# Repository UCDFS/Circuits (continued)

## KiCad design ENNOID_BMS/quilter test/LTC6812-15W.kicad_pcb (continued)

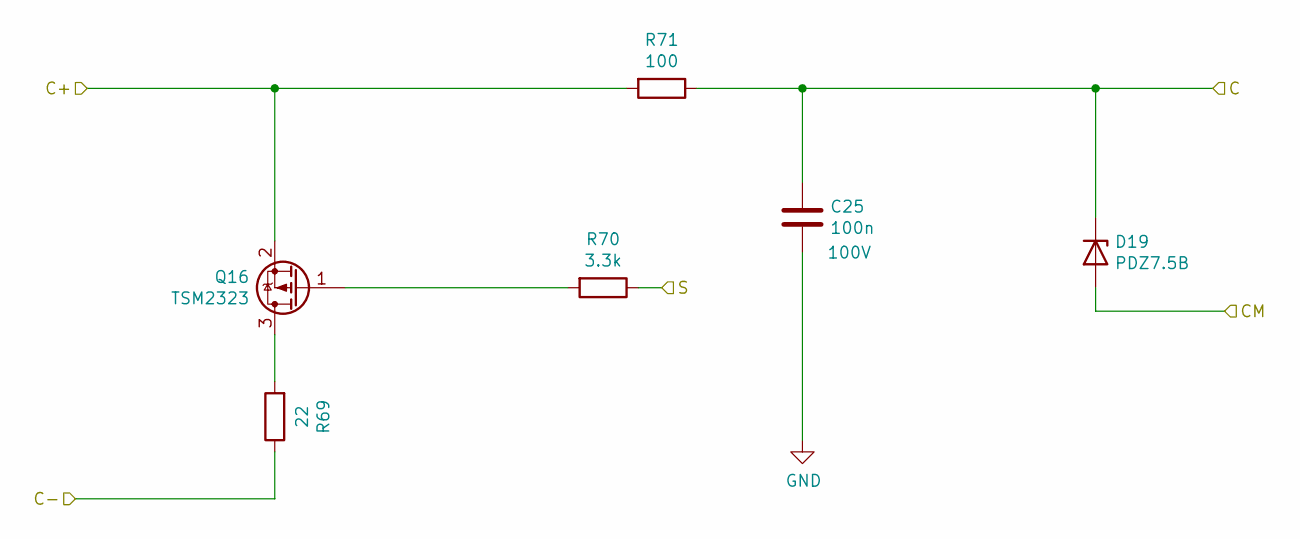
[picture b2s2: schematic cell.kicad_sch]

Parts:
C25: 100n; C_0603_1608Metric; Voltage 100V; Part Number GRM188R72A104KA35D
D19: PDZ7.5B; D_SOD-323; Part Number PDZ7.5B
Q16: TSM2323; SOT-23; Part Number TSM2323
R69: 22; R_2512_6332Metric; Part Number AC2512JK-7W22RL
R70: 3.3k; R_0603_1608Metric; Part Number CRCW06033K30FKEA
R71: 100; R_0603_1608Metric; Part Number CRCW0603100RFKEA

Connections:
/cell14/C: D19.2 (A); also elsewhere on the board
/cell15/C: C25.2, D19.1 (K), R71.1; also elsewhere on the board
/cell15/S: R70.1; also elsewhere on the board
Cell_1-: C25.1; also elsewhere on the board
Cell_14+: R69.1; also elsewhere on the board
Cell_15+: Q16.2 (S), R71.2; also elsewhere on the board
unnamed: Q16.3 (D), R69.2
unnamed: Q16.1 (G), R70.2

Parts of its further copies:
C11, C12, C13, C14, C15, C16, C17, C18, C19, C20, C21, C22, C23, C24: 100n; C_0603_1608Metric; Voltage 100V; Part Number GRM188R72A104KA35D
D5, D6, D7, D8, D9, D10, D11, D12, D13, D14, D15, D16, D17, D18: PDZ7.5B; D_SOD-323; Part Number PDZ7.5B
Q2, Q3, Q4, Q5, Q6, Q7, Q8, Q9, Q10, Q11, Q12, Q13, Q14, Q15: TSM2323; SOT-23; Part Number TSM2323
R13, R17, R21, R25, R29, R33, R37, R41, R45, R49, R53, R57, R61, R65: 22; R_2512_6332Metric; Part Number AC2512JK-7W22RL
R14, R18, R22, R26, R30, R34, R38, R42, R46, R50, R54, R58, R62, R66: 3.3k; R_0603_1608Metric; Part Number CRCW06033K30FKEA
R15, R19, R23, R27, R31, R35, R39, R43, R47, R51, R55, R59, R63, R67: 100; R_0603_1608Metric; Part Number CRCW0603100RFKEA

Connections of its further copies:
/cell1/C: C11.2, D5.1 (K), D6.2 (A), R15.1; also elsewhere on the board
/cell1/S: R14.1; also elsewhere on the board
/cell2/C: C12.2, D6.1 (K), D7.2 (A), R19.1; also elsewhere on the board
/cell2/S: R18.1; also elsewhere on the board
/cell3/C: C13.2, D7.1 (K), D8.2 (A), R23.1; also elsewhere on the board
/cell3/S: R22.1; also elsewhere on the board
/cell4/C: C14.2, D8.1 (K), D9.2 (A), R27.1; also elsewhere on the board
/cell4/S: R26.1; also elsewhere on the board
/cell5/C: C15.2, D9.1 (K), D10.2 (A), R31.1; also elsewhere on the board
/cell5/S: R30.1; also elsewhere on the board
/cell6/C: C16.2, D10.1 (K), D11.2 (A), R35.1; also elsewhere on the board
/cell6/S: R34.1; also elsewhere on the board
/cell7/C: C17.2, D11.1 (K), D12.2 (A), R39.1; also elsewhere on the board
/cell7/S: R38.1; also elsewhere on the board
/cell8/C: C18.2, D12.1 (K), D13.2 (A), R43.1; also elsewhere on the board
/cell8/S: R42.1; also elsewhere on the board
/cell9/S: R46.1; also elsewhere on the board
/cell10/C: C20.2, D14.1 (K), D15.2 (A), R51.1; also elsewhere on the board
/cell10/CM: C19.2, D13.1 (K), D14.2 (A), R47.1; also elsewhere on the board
/cell10/S: R50.1; also elsewhere on the board
/cell11/C: C21.2, D15.1 (K), D16.2 (A), R55.1; also elsewhere on the board
/cell11/S: R54.1; also elsewhere on the board
/cell12/C: C22.2, D16.1 (K), D17.2 (A), R59.1; also elsewhere on the board
/cell12/S: R58.1; also elsewhere on the board
/cell13/C: C23.2, D17.1 (K), D18.2 (A), R63.1; also elsewhere on the board
/cell13/S: R62.1; also elsewhere on the board
/cell14/C: C24.2, D18.1 (K), R67.1; also elsewhere on the board
/cell14/S: R66.1; also elsewhere on the board
Cell_1+: Q2.2 (S), R15.2, R17.1; also elsewhere on the board
Cell_1-: C11.1, C12.1, C13.1, C14.1, C15.1, C16.1, C17.1, C18.1, C19.1, C20.1, C21.1, C22.1, C23.1, C24.1, D5.2 (A), R13.1; also elsewhere on the board
Cell_2+: Q3.2 (S), R19.2, R21.1; also elsewhere on the board
Cell_3+: Q4.2 (S), R23.2, R25.1; also elsewhere on the board
Cell_4+: Q5.2 (S), R27.2, R29.1; also elsewhere on the board
Cell_5+: Q6.2 (S), R31.2, R33.1; also elsewhere on the board
Cell_6+: Q7.2 (S), R35.2, R37.1; also elsewhere on the board
Cell_7+: Q8.2 (S), R39.2, R41.1; also elsewhere on the board
Cell_8+: Q9.2 (S), R43.2, R45.1; also elsewhere on the board
Cell_9+: Q10.2 (S), R47.2, R49.1; also elsewhere on the board
Cell_10+: Q11.2 (S), R51.2, R53.1; also elsewhere on the board
Cell_11+: Q12.2 (S), R55.2, R57.1; also elsewhere on the board
Cell_12+: Q13.2 (S), R59.2, R61.1; also elsewhere on the board
Cell_13+: Q14.2 (S), R63.2, R65.1; also elsewhere on the board
Cell_14+: Q15.2 (S), R67.2; also elsewhere on the board
unnamed: Q2.3 (D), R13.2
unnamed: Q2.1 (G), R14.2
unnamed: Q3.3 (D), R17.2
unnamed: Q3.1 (G), R18.2
unnamed: Q4.3 (D), R21.2
unnamed: Q4.1 (G), R22.2
unnamed: Q5.3 (D), R25.2
unnamed: Q5.1 (G), R26.2
unnamed: Q6.3 (D), R29.2
unnamed: Q6.1 (G), R30.2
unnamed: Q7.3 (D), R33.2
unnamed: Q7.1 (G), R34.2
unnamed: Q8.3 (D), R37.2
unnamed: Q8.1 (G), R38.2
unnamed: Q9.3 (D), R41.2
unnamed: Q9.1 (G), R42.2
unnamed: Q10.3 (D), R45.2
unnamed: Q10.1 (G), R46.2
unnamed: Q11.3 (D), R49.2
unnamed: Q11.1 (G), R50.2
unnamed: Q12.3 (D), R53.2
unnamed: Q12.1 (G), R54.2
unnamed: Q13.3 (D), R57.2
unnamed: Q13.1 (G), R58.2
unnamed: Q14.3 (D), R61.2
unnamed: Q14.1 (G), R62.2
unnamed: Q15.3 (D), R65.2
unnamed: Q15.1 (G), R66.2

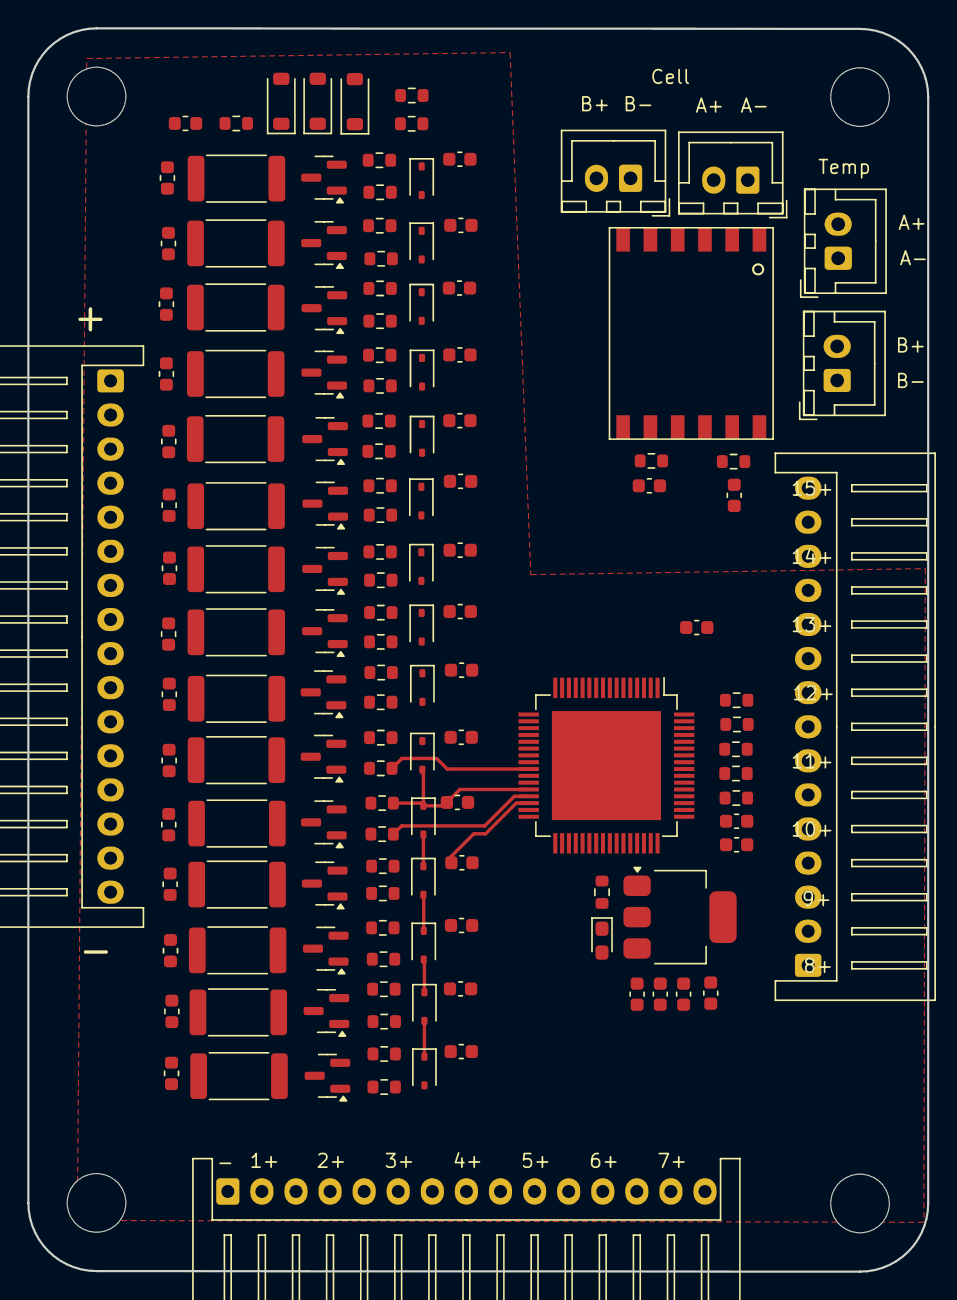
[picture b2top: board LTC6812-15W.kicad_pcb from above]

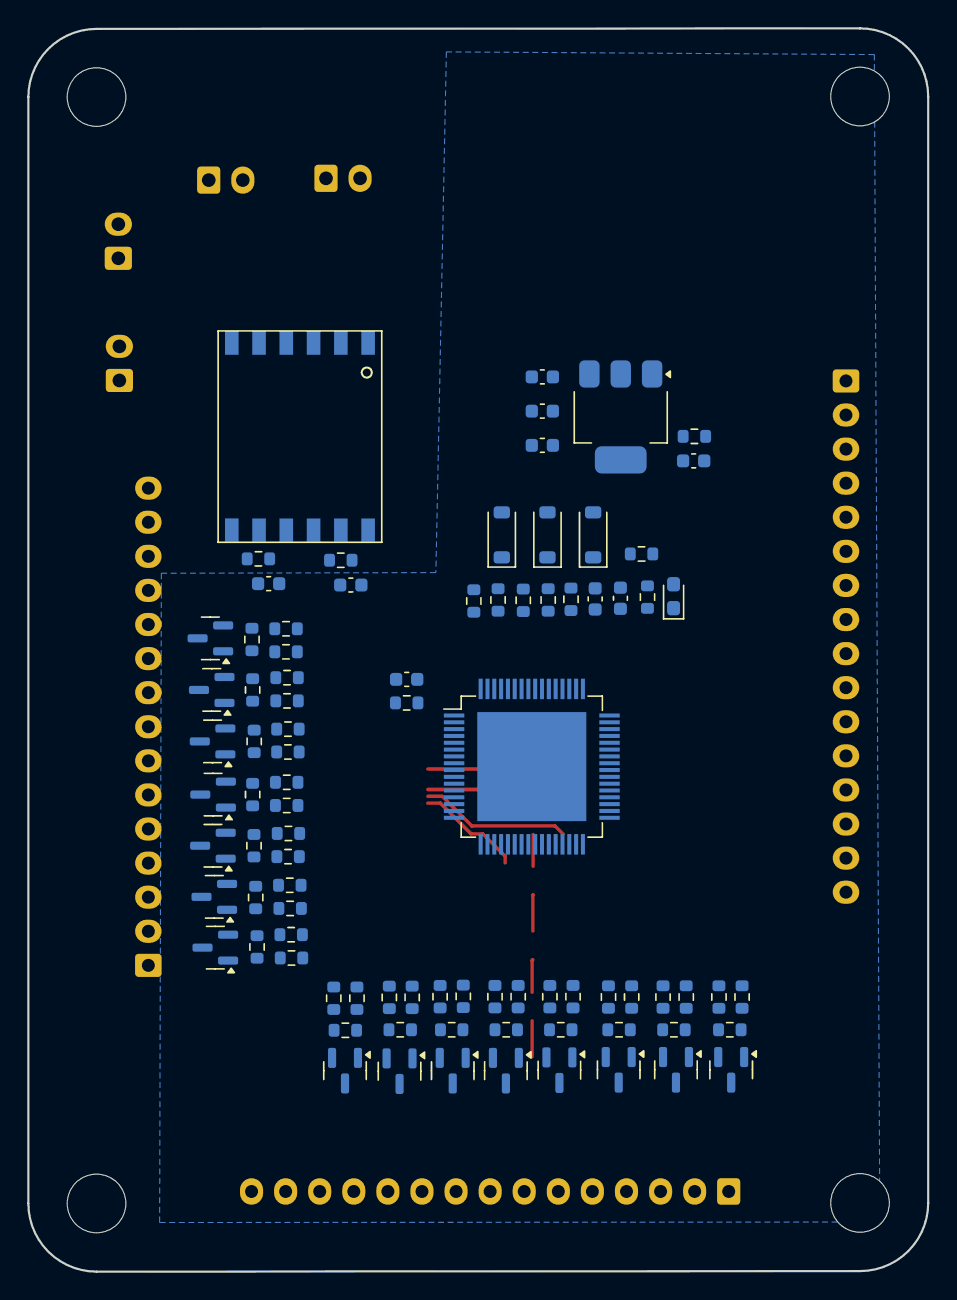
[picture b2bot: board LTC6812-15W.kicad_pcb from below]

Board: 2 copper layers, 66.0 x 91.2 mm, 227 parts (87 on the bottom side), 213 nets.

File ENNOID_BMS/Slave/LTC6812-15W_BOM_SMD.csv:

Reference,Qty,Value,DNP,Exclude from Board,Footprint,Datasheet,Part Number
"C1,C4,C10,C11,C12,C13,C14,C15,C16,C17,C18,C19,C20,C21,C22,C23,C24,C25,C28",19,100n,,,Capacitor_SMD:C_0603_1608Metric,https://pim.murata.com/asset/pim4/ceramicCapacitorSMD/GRM188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,GRM188R72A104KA35D
"C2,C3,C5,C6,C7,C26,C27,C29,C30,C31",10,1uF,,,Capacitor_SMD:C_0603_1608Metric,https://mm.digikey.com/Volume0/opasdata/d220001/medias/docus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,CL10B105KP8NNNC
"C8,C9,C32,C33",4,100p,,,Capacitor_SMD:C_0603_1608Metric,https://pim.murata.com/asset/pim4/ceramicCapacitorSMD/GRM188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,GRM1885C1H101JA01D
"D1,D2,D20,D21",4,1N4148W,,,Diode_SMD:D_SOD-123,https://www.mouser.ie/datasheet/3/175/1/BAV16W_1N4148W.pdf,1N4148W-7-F
"D3,D22",2,MMSZ5268BT1G,,,Diode_SMD:D_SOD-123,https://www.onsemi.com/pub/Collateral/MMSZ5221BT1-D.PDF,MMSZ5268BT1G
"D4,D23",2,LED,,,LED_SMD:LED_0603_1608Metric_Pad1.05x0.95mm_HandSolder,https://www.vishay.com/doc?84393,VLMTG1400-GS08
"D5,D6,D7,D8,D9,D10,D11,D12,D13,D14,D15,D16,D17,D18,D19",15,PDZ7.5B,,,Diode_SMD:D_SOD-323,https://assets.nexperia.com/documents/data-sheet/PDZ-B_SER.pdf,PDZ7.5B
"F4,F5,F6,F7,F8,F9,F10,F11,F12,F13,F14,F15,F16,F17,F18,F19",16,0.25A,,,Fuse:Fuse_0603_1608Metric,https://www.littelfuse.com/assetdocs/littelfuse_fuse_438_dat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,0438.250WR
"FB1,FB2",2,33,,,Resistor_SMD:R_0603_1608Metric,https://www.mouser.ie/datasheet/3/76/1/ENFA0003.pdf,BLM18PG330SN1D
"Q1,Q17",2,DZTT5551,,,Package_TO_SOT_SMD:SOT-223,https://www.mouser.ie/datasheet/3/175/1/ds31219.pdf,DZT5551-13
"Q2,Q3,Q4,Q5,Q6,Q7,Q8,Q9,Q10,Q11,Q12,Q13,Q14,Q15,Q16",15,TSM2323,,,Package_TO_SOT_SMD:SOT-23,https://www.taiwansemi.com/assets/datasheet/pdf.php?pn=TSM2323CX,TSM2323
"R1,R3,R8,R9,R15,R19,R23,R27,R31,R35,R39,R43,R47,R51,R55,R59,R63,R67,R71,R74,R76,R81,R82,R84,R85,R86,R87,R88,R89,R90,R91,R92,R93,R94,R95,R96,R98,R99",38,100,,,Resistor_SMD:R_0603_1608Metric,https://www.vishay.com/docs/20035/dcrcwe3.pdf,CRCW0603100RFKEA
"R2,R75",2,806,,,Resistor_SMD:R_0603_1608Metric,https://www.vishay.com/docs/20035/dcrcwe3.pdf,CRCW0603806RFKEA
"R4,R77",2,1M,,,Resistor_SMD:R_0603_1608Metric,https://www.vishay.com/docs/20035/dcrcwe3.pdf,CRCW06031M00FKEA
"R5,R10,R78,R83",4,1.2k,,,Resistor_SMD:R_0603_1608Metric,https://www.vishay.com/docs/20035/dcrcwe3.pdf,CRCW06031K20FKEA
"R6,R7,R79,R80",4,0,,,Resistor_SMD:R_0603_1608Metric,https://www.vishay.com/docs/20035/dcrcwe3.pdf,CRCW06030000Z0EA
"R11,R12,R16,R20,R24,R28,R32,R36,R40,R44,R48,R52,R56,R60,R64",15,680,,,Resistor_SMD:R_0603_1608Metric,https://www.vishay.com/docs/20035/dcrcwe3.pdf,CRCW0603680RFKEA
"R13,R17,R21,R25,R29,R33,R37,R41,R45,R49,R53,R57,R61,R65,R69",15,22,,,Resistor_SMD:R_2512_6332Metric,https://www.mouser.ie/datasheet/3/508/1/PYu-AC_51_RoHS_L_11.pdf,AC2512JK-7W22RL
"R14,R18,R22,R26,R30,R34,R38,R42,R46,R50,R54,R58,R62,R66,R70",15,3.3k,,,Resistor_SMD:R_0603_1608Metric,https://www.vishay.com/docs/20035/dcrcwe3.pdf,CRCW06033K30FKEA
"TR1,TR2",2,HM2102NL,,,ENNOID:HM2102NL,https://www.mouser.ie/datasheet/3/508/1/HM2102NL.pdf,HM2102NL
"U1,U2",2,LTC6812-1,,,ENNOID:TQFP-64-1EP_10x10mm_P0.5mm_EP8x8mm,https://www.analog.com/media/en/technical-documentation/data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,LTC6812-1

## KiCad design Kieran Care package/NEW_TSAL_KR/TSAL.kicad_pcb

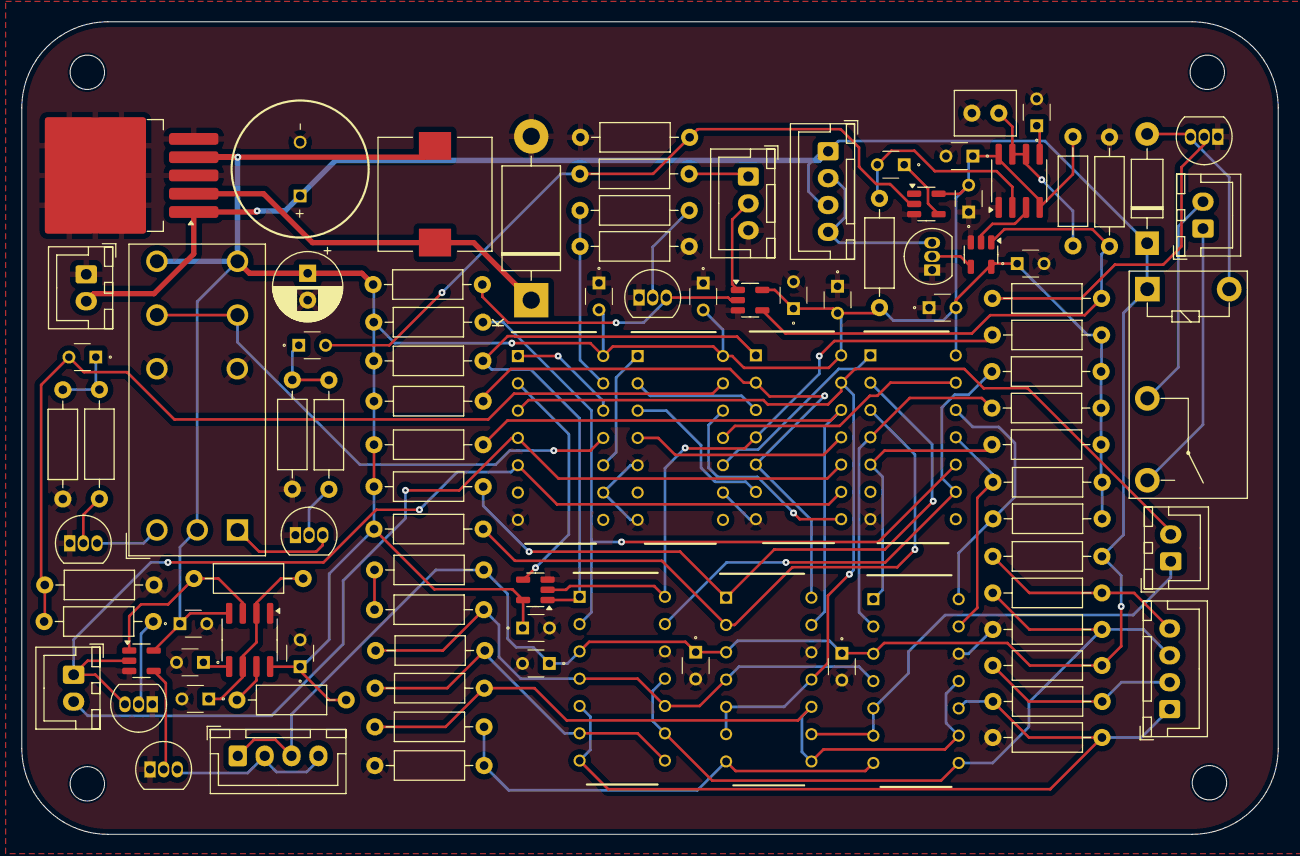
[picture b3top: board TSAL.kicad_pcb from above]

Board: 2 copper layers, 116.9 x 75.6 mm, 99 parts (0 on the bottom side), 71 nets.

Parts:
C1, C11, C28: 1uF; FA18X7R1H104KNU00
C2, C3, C4, C5, C6, C7, C8, C12, C13, C14, C16, C17, C22, C25, C26: 0.1uF; FA18X7R1H104KNU00
C9, C24: 10nF; FA18X7R1H104KNU00
C15: 220uF; CP_Radial_D6.3mm_P2.50mm
C18: 680uF; CAPPRD500W60D1275H2700
C23: 22uF; C_Disc_D5.5mm_W4mm_P2.50mm_1
D1: 1N4001; D_DO-41_SOD81_P10.16mm_Horizontal
D3: 1N5821; D_DO-201AD_P15.24mm_Horizontal
IC1, IC4, IC5: CD4072BE; DIP794W53P254L1930H508Q14N
IC3: SN74HC86N; DIP794W53P254L1930H508Q14N
J1, J4, J5: B4B-XH-A; JST_XH_B4B-XH-A_1x04_P2.50mm_Vertical
J2: B3B-XH-A; JST_XH_B3B-XH-A_1x03_P2.50mm_Vertical
J3, J6, J7, J8: B2B-XH-A; JST_XH_B2B-XH-A_1x02_P2.50mm_Vertical
K1: G5RL-K1-E-DC5; Relay-G5RL-K1-E
K2: G5Q1A4DC12; Relay_SPST_Omron-G5Q-1A
L1: 33uH; L_10.4x10.4_H4.8
Q1, Q2, Q3, Q4, Q5, Q6, Q7: 2N7000; TO-92_Inline
R1: 47k; R_Axial_DIN0207_L6.3mm_D2.5mm_P10.16mm_Horizontal
R2, R10, R11, R13, R14: 27k; R_Axial_DIN0207_L6.3mm_D2.5mm_P10.16mm_Horizontal
R3: 15k; R_Axial_DIN0207_L6.3mm_D2.5mm_P10.16mm_Horizontal
R4, R6, R51: 4.7k; R_Axial_DIN0207_L6.3mm_D2.5mm_P10.16mm_Horizontal
R5: 20k; R_Axial_DIN0207_L6.3mm_D2.5mm_P10.16mm_Horizontal
R7, R25, R36, R43, R44: 100; R_Axial_DIN0207_L6.3mm_D2.5mm_P10.16mm_Horizontal
R8, R23, R26, R39, R46: 10k; R_Axial_DIN0207_L6.3mm_D2.5mm_P10.16mm_Horizontal
R9, R12, R41, R42: 68k; R_Axial_DIN0207_L6.3mm_D2.5mm_P10.16mm_Horizontal
R15, R16, R17, R18, R19, R20, R21, R22, R29, R30, R31, R32: 5k6; R_Axial_DIN0207_L6.3mm_D2.5mm_P10.16mm_Horizontal
R24: 220k; R_Axial_DIN0207_L6.3mm_D2.5mm_P10.16mm_Horizontal
R27: 100k; R_Axial_DIN0207_L6.3mm_D2.5mm_P10.16mm_Horizontal
R40: 1k; R_Axial_DIN0207_L6.3mm_D2.5mm_P10.16mm_Horizontal
R50: 6k8; R_Axial_DIN0207_L6.3mm_D2.5mm_P10.16mm_Horizontal
U1, U7: SN74AHC1G32TDBVRQ1; SOT-23-5
U2, U6: LMC555CMX/NOPB; SOIC-8_3.9x4.9mm_P1.27mm
U3, U4, U5: LM339N/NOPB; DIP794W53P254L1930H508Q14N
U8, U14: SN74AHCT1G08DBVR; SOT-23-5
U9: SN74AHC1G04DBVRE4; SOT-23-5
U26: LM2596SX-5.0/NOPB; TO-263-5_TabPin3

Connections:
0V5th: R5.1, R6.2, U4.7 (+), U5.7 (+)
2V5th: R4.1, R5.2, U4.8 (-), U4.10 (-), U5.9 (+), U5.11 (+)
3Vth: R3.1, R4.2, U3.6 (-), U3.8 (-)
4V5th: R2.1, R3.2, U3.4 (-), U3.10 (-), U4.4 (-), U5.4 (-)
5V: C2.1, C4.2, C6.1, C7.1, C8.2, C13.1, C14.1, C15.1, C16.2, C17.2, C22.1, C26.2, IC1.14 (VDD), IC3.14 (VCC), IC4.14 (VDD), IC5.14 (VDD), K1.4, K1.5, K1.9, L1.2, R15.2, R16.2, R17.2, R18.2, R19.2, R20.2, R21.2, R22.2, R23.1, R27.1, R29.2, R30.2, R31.2, R32.2, R40.2, R46.1, U1.5 (VCC), U2.4 (R), U2.8 (VCC), U6.4 (R), U6.8 (VCC), U7.5 (VCC), U8.5 (VCC), U9.5 (VCC), U14.5 (VCC), U26.4 (FB)
7Vth: R1.1, R2.2
12V: C3.1, C5.1, C12.1, C18.1 (+), D1.1 (K), J4.1, J4.3, J5.1, J5.3, J6.2, K2.1, R1.2, R9.2, R12.2, U3.3 (V+), U4.3 (V+), U5.3 (V+), U26.1 (VIN)
A1: J1.1, R10.1, R11.2, U3.5 (+), U3.7 (+), U5.10 (-)
A2: J1.3, R13.1, R14.2, U3.9 (+), U3.11 (+), U5.8 (-)
AIR1_aux+: J1.2, R9.1, R10.2
AIR2_aux+: J1.4, R12.1, R13.2
AIR_CON_FAULT: IC4.10 (F), IC5.1 (J=A+B+C+D)
BATT_FAULT: IC3.8 (3Y), IC4.12 (H)
CON_buf: IC3.12 (4A), R21.1, U4.13
CON_imp: IC3.11 (4Y), IC4.4 (C)
GLVS 5V+: C28.2, R50.2, R51.1, U9.2
GLVS+: J2.1, R50.1
GLVS-: C2.2, C3.2, C4.1, C5.2, C6.2, C7.2, C8.1, C9.2, C11.2, C12.2, C13.2, C14.2, C15.2, C16.1, C17.1, C18.2 (-), C22.2, C23.1, C24.2, C26.1, D3.2 (A), IC1.7 (VSS), IC1.9 (E), IC3.7 (GND), IC4.5 (D), IC4.7 (VSS), IC4.9 (E), IC5.7 (VSS), J2.3, J6.1, K1.2, K1.7, Q1.1 (S), Q2.1 (S), Q3.1 (S), Q4.1 (S), Q5.1 (S), Q6.1 (S), Q7.1 (S), R6.1, R8.2, R11.1, R14.1, R26.1, R39.1, R41.1, R42.2, R51.2, U1.3 (GND), U2.1 (GND), U3.12 (V-), U4.12 (V-), U5.12 (V-), U6.1 (GND), U7.3 (GND), U8.3 (GND), U9.3 (GND), U14.3 (GND), U26.3 (GND), U26.5 (~ON/OFF)
IMP_FAULT: IC1.10 (F), IC4.1 (J=A+B+C+D)
unnamed: C1.1, R41.2, R43.2
unnamed: C25.1, U9.4
unnamed: C28.1, R42.1, R44.2
unnamed: D1.2 (A), K2.5, Q5.3 (D)
unnamed: D3.1 (K), L1.1, U26.2 (OUT)
unnamed: Q1.2 (G), R25.2
unnamed: Q2.2 (G), U8.4
unnamed: Q3.3 (D), R40.1, U14.2
unnamed: Q3.2 (G), R36.2
unnamed: Q4.2 (G), U7.4
unnamed: Q5.2 (G), R7.2
unnamed: K1.1, Q6.3 (D)
unnamed: Q6.2 (G), R44.1
unnamed: K1.8, Q7.3 (D)
unnamed: Q7.2 (G), R43.1
unnamed: C24.1, U2.5 (CV)
unnamed: C23.2, R27.2, U2.6 (THR), U2.7 (DIS)
unnamed: U2.3 (Q), U7.2
unnamed: C25.2, R46.2, U2.2 (TR)
unnamed: C9.1, U6.5 (CV)
unnamed: R23.2, U6.7 (DIS)
unnamed: R24.1, U6.3 (Q), U8.1
unnamed: C11.1, R24.2, U6.2 (TR), U6.6 (THR)
OPEN_CON: IC5.2 (A), R20.1, U4.1
OPEN_~AIR: IC5.5 (D), R30.1, U5.1
Precharge_ON: IC1.3 (B), IC3.13 (4B), J8.2, U4.5 (+), U4.6 (-), U4.11 (+)
Precharge_done/Close_AIR1: J8.1, U4.9 (+), U5.5 (+), U5.6 (-)
SCS_FAULT: C1.2, IC4.13 (K=E+F+G+H), R25.1, R26.2
SCS_LATCH: IC1.11 (G), K1.3, K1.6
SHORT_CON: IC5.3 (B), R19.1, U4.2
SHORT_~AIR: IC5.4 (C), R29.1, U5.2
TS<60V: J2.2, U14.1
TS>60V (1): IC1.4 (C), IC3.10 (3B), J3.2
TS>60V (2): IC1.5 (D), IC3.9 (3A), J3.1, Q1.3 (D), U8.2
TSAL_OK: R7.1, R8.1, U7.1, U14.4
TSAL_OK_Shutdown+: J7.1, K2.3
TSAL_OK_Shutdown-: J7.2, K2.2
TS_active: IC1.1 (J=A+B+C+D), IC1.12 (H)
air1_imp: IC3.3 (1Y), IC4.2 (A)
air2_imp: IC3.6 (2Y), IC4.3 (B)
closed_air: IC1.2 (A), U1.4
closed_air1: IC3.1 (1A), R16.1, U1.1, U3.1
closed_air2: IC3.4 (2A), R18.1, U1.2, U3.14
green-: J5.2, J5.4, Q4.3 (D)
not_green: IC1.13 (K=E+F+G+H), R36.1, R39.2
red-: J4.2, J4.4, Q2.3 (D)
short_air: IC4.11 (G), IC5.13 (K=E+F+G+H)
short_air1: IC5.10 (F), R15.1, U3.2
short_air2: IC5.9 (E), R17.1, U3.13
short_gnd_a1: IC5.11 (G), R31.1, U5.13
short_gnd_a2: IC5.12 (H), R32.1, U5.14
~AIR_buf: IC3.2 (1B), IC3.5 (2B), R22.1, U4.14

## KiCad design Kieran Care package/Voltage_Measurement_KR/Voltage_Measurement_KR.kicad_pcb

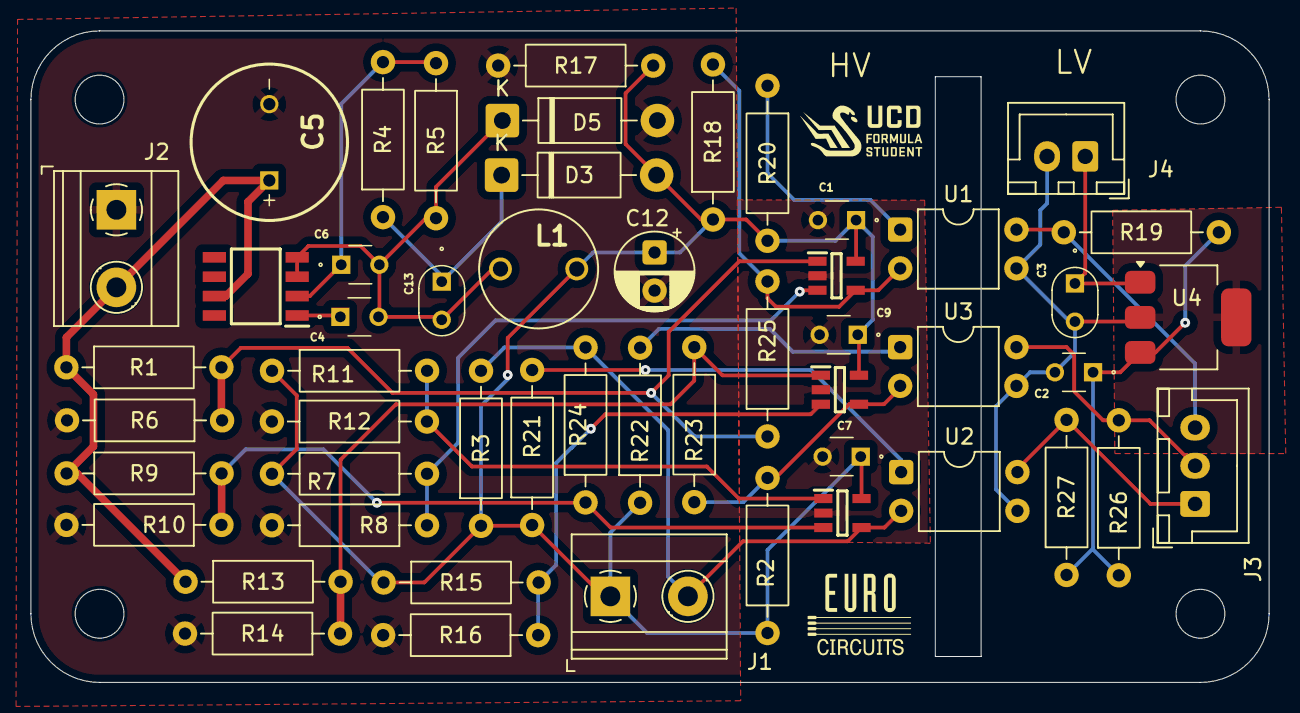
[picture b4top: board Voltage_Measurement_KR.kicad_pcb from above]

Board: 2 copper layers, 81.2 x 42.7 mm, 52 parts (0 on the bottom side), 25 nets.

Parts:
C1, C2, C7, C9: 0.1uF; FA18X7R1H104KNU00
C3, C13: 0.22uF; FA14X7R1H224KNU00
C4: 1uF; FA18X7R1H104KNU00
C5: 10uF 400VDC; CAPPRD500W60D1025H2200
C6: 470pF; FA18X7R1H104KNU00
C12: 10uF; CP_Radial_D5.0mm_P2.50mm
D3, D5: STTH1R06; D_DO-41_SOD81_P10.16mm_Horizontal
IC1: MP9488GS-P; SOIC127P600X175-8N
IC2, IC3, IC4: TLV1701AIDBVT; SOT95P280X145-5N
J1, J2: Conn_01x02_Phoenix; Phoenix_1x2_1729128
J3: Conn_01x03_Pin; JST_XH_B3B-XH-A_1x03_P2.50mm_Vertical
J4: Conn_01x02_Pin; JST_XH_B2B-XH-A_1x02_P2.50mm_Vertical
L1: 1.2mH; WE-TI_809589
R1, R9, R13: 560k; R_Axial_DIN0207_L6.3mm_D2.5mm_P10.16mm_Horizontal
R2, R3, R18: 100K; R_Axial_DIN0207_L6.3mm_D2.5mm_P10.16mm_Horizontal
R4, R6, R10, R14: 18k; R_Axial_DIN0207_L6.3mm_D2.5mm_P10.16mm_Horizontal
R5: 4.7k; R_Axial_DIN0207_L6.3mm_D2.5mm_P10.16mm_Horizontal
R7, R11, R15: 56k; R_Axial_DIN0207_L6.3mm_D2.5mm_P10.16mm_Horizontal
R8, R12, R16: 10k; R_Axial_DIN0207_L6.3mm_D2.5mm_P10.16mm_Horizontal
R17: 2.7k; R_Axial_DIN0207_L6.3mm_D2.5mm_P10.16mm_Horizontal
R19, R26, R27: 10K; R_Axial_DIN0207_L6.3mm_D2.5mm_P10.16mm_Horizontal
R20, R21, R22: 2.2K; R_Axial_DIN0207_L6.3mm_D2.5mm_P10.16mm_Horizontal
R23, R24, R25: 1.5M; R_Axial_DIN0207_L6.3mm_D2.5mm_P10.16mm_Horizontal
U1, U2, U3: HCPL-817-000E; DIP-4_W7.62mm
U4: LM7805_SOT223; SOT-223-3_TabPin2

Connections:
5V: C2.1, R19.1, R26.1, R27.1, U4.3 (VO)
12.3V: C1.1, C7.1, C9.1, C12.1, D3.2 (A), IC2.5 (V+), IC3.5 (V+), IC4.5 (V+), J1.1, L1.1, R2.1, R3.1, R7.1, R11.1, R15.1, R17.1, R18.1, R20.2, R21.1, R22.1
60V_REF_1: IC2.3 (IN-), R7.2, R8.1
60V_REF_2: IC3.1 (IN+), R11.2, R12.1
60V_REF_3: IC4.3 (IN-), R15.2, R16.1
300V_REF_1: IC2.1 (IN+), R1.2, R6.1, R25.1
300V_REF_2: IC3.3 (IN-), R9.2, R10.1, R24.1
300V_REF_3: IC4.1 (IN+), R13.2, R14.1, R23.1
GLV+: C3.1, J4.1, U4.1 (VI)
GLV-: C2.2, C3.2, J4.2, U1.3, U2.3, U3.3, U4.2 (GND)
LED-: IC3.4 (OUT), J1.2, R3.2, R24.2, U2.2
unnamed: C13.1, D3.1 (K), R4.1
unnamed: C4.2, C6.2, C13.2, D5.1 (K), IC1.3 (SW_1), IC1.4 (SW_2), L1.2, R5.2
unnamed: C6.1, IC1.2 (FB), R4.2, R5.1
unnamed: C4.1, IC1.1 (VCC)
unnamed: IC2.4 (OUT), R18.2, R25.2, U1.2
unnamed: IC4.4 (OUT), R2.2, R23.2, U3.2
unnamed: R20.1, U1.1
unnamed: R21.2, U2.1
unnamed: R22.2, U3.1
TS+: C5.1 (+), IC1.7 (VIN), J2.2, R1.1, R9.1, R13.1
TS-: C1.2, C5.2 (-), C7.2, C9.2, C12.2, D5.2 (A), IC2.2 (V-), IC3.2 (V-), IC4.2 (V-), J2.1, R6.2, R8.2, R10.2, R12.2, R14.2, R16.2, R17.2
TS<60V: J3.1, R27.2, U2.4
TS>60V (1): J3.3, R19.2, U1.4
TS>60V (2): J3.2, R26.2, U3.4

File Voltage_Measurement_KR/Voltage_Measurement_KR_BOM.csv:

"Reference","Value","Part number","Datasheet","Footprint","Qty","DNP","Part Number"
"C1,C2,C7,C9,C10,C11,C14","0.1uF","FA18X7R1H104KNU00","https://www.farnell.com/datasheets/2923220.pdf","FA14_Capacitor:FA18X7R1H104KNU00","7","",""
"C3,C13","0.22uF","FA14X7R1H224KNU00","https://www.farnell.com/datasheets/2923220.pdf","FA14_Capacitor:FA14X7R1H224KNU00","2","",""
"C4","1uF","FA18X7R1E105KRU00","https://www.farnell.com/datasheets/2923220.pdf","FA14_Capacitor:FA18X7R1H104KNU00","1","",""
"C5","10uF 400VDC","400BXC10MEFC10X20","http://www.farnell.com/datasheets/2321684.pdf","400BXC10MEFC10X20:CAPPRD500W60D1025H2200","1","",""
"C6","470pF","FA18C0G1H471JNU00","https://www.farnell.com/datasheets/2923220.pdf","FA14_Capacitor:FA18X7R1H104KNU00","1","",""
"C12","10uF","ECE-A1EKS100I","https://industrial.panasonic.com/cdbs/www-data/pdf/RDF0000/A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","Capacitor_THT:CP_Radial_D5.0mm_P2.50mm","1","",""
"D3,D5","STTH1R06","STTH1R06","https://www.mouser.ie/datasheet/2/389/stth1r06-1851882.pdf","Diode_THT:D_DO-41_SOD81_P10.16mm_Horizontal","2","",""
"IC1","MP9488GS-P","MP9488GS-P","https://www.monolithicpower.com/en/documentview/productdocum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","MP9488GS-Z:SOIC127P600X175-8N","1","",""
"IC2,IC3,IC4","TLV1701AIDBVT","TLV1701AIDBVT","http://www.ti.com/lit/gpn/tlv1701","TLV1701AIDBVT:SOT95P280X145-5N","3","",""
"J1,J2","Conn_01x02_Phoenix","1729128","https://www.phoenixcontact.com/en-us/products/printed-circui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","Phoenix 1x2 Connector:Phoenix_1x2_1729128","2","",""
"J3","Conn_01x03_Pin","B3B-XH-A","https://www.jst-mfg.com/product/pdf/eng/eXH.pdf","Connector_JST:JST_XH_B3B-XH-A_1x03_P2.50mm_Vertical","1","",""
"J4","Conn_01x02_Pin","B2B-XH-A","https://www.jst-mfg.com/product/pdf/eng/eXH.pdf","Connector_JST:JST_XH_B2B-XH-A_1x02_P2.50mm_Vertical","1","",""
"L1","1.2mH","7447720122","https://www.we-online.com/components/products/datasheet/7447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","Inductor_7447720122:WE-TI_809589","1","",""
"Q1,Q2","2N7000","2N7000","https://www.onsemi.com/download/data-sheet/pdf/nds7002a-d.pdf","Package_TO_SOT_THT:TO-92_Inline","2","",""
"R1,R9,R13","560k","MCF 0.25W 560K","https://www.farnell.com/datasheets/3436052.pdf?_gl=1*1pxxutc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","Resistor_THT:R_Axial_DIN0207_L6.3mm_D2.5mm_P10.16mm_Horizontal","3","",""
"R2,R3,R18,R19,R20,R26,R27","1K","MCF 0.25W 1K","https://www.farnell.com/datasheets/3436052.pdf?_gl=1*1pxxutc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","Resistor_THT:R_Axial_DIN0207_L6.3mm_D2.5mm_P10.16mm_Horizontal","7","",""
"R4,R6,R10,R14","18k","MCF 0.25W 18K","https://www.farnell.com/datasheets/3436052.pdf?_gl=1*1pxxutc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","Resistor_THT:R_Axial_DIN0207_L6.3mm_D2.5mm_P10.16mm_Horizontal","4","",""
"R5","4.7k","MCF 0.25W 4.7K","https://www.farnell.com/datasheets/3436052.pdf?_gl=1*1pxxutc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","Resistor_THT:R_Axial_DIN0207_L6.3mm_D2.5mm_P10.16mm_Horizontal","1","",""
"R7,R11,R15","56k","MCF 0.25W 56K","https://www.farnell.com/datasheets/3436052.pdf?_gl=1*1pxxutc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","Resistor_THT:R_Axial_DIN0207_L6.3mm_D2.5mm_P10.16mm_Horizontal","3","",""
"R8,R12,R16","10k","MCF 0.25W 10K","https://www.farnell.com/datasheets/3436052.pdf?_gl=1*1pxxutc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","Resistor_THT:R_Axial_DIN0207_L6.3mm_D2.5mm_P10.16mm_Horizontal","3","",""
"R17","2.7k","MCF 0.25W 2K7","https://www.farnell.com/datasheets/3436052.pdf?_gl=1*1pxxutc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","Resistor_THT:R_Axial_DIN0207_L6.3mm_D2.5mm_P10.16mm_Horizontal","1","",""
"U1,U2,U3","HCPL-817-000E","HCPL-817-000E","https://www.mouser.ie/datasheet/2/678/AV02_0265EN_2021_04_26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","Package_DIP:DIP-4_W7.62mm","3","",""
"U4","LM7805_SOT223","LM7805MPX/NOPB","https://www.ti.com/lit/gpn/lm7800","Package_TO_SOT_SMD:SOT-223-3_TabPin2","1","",""

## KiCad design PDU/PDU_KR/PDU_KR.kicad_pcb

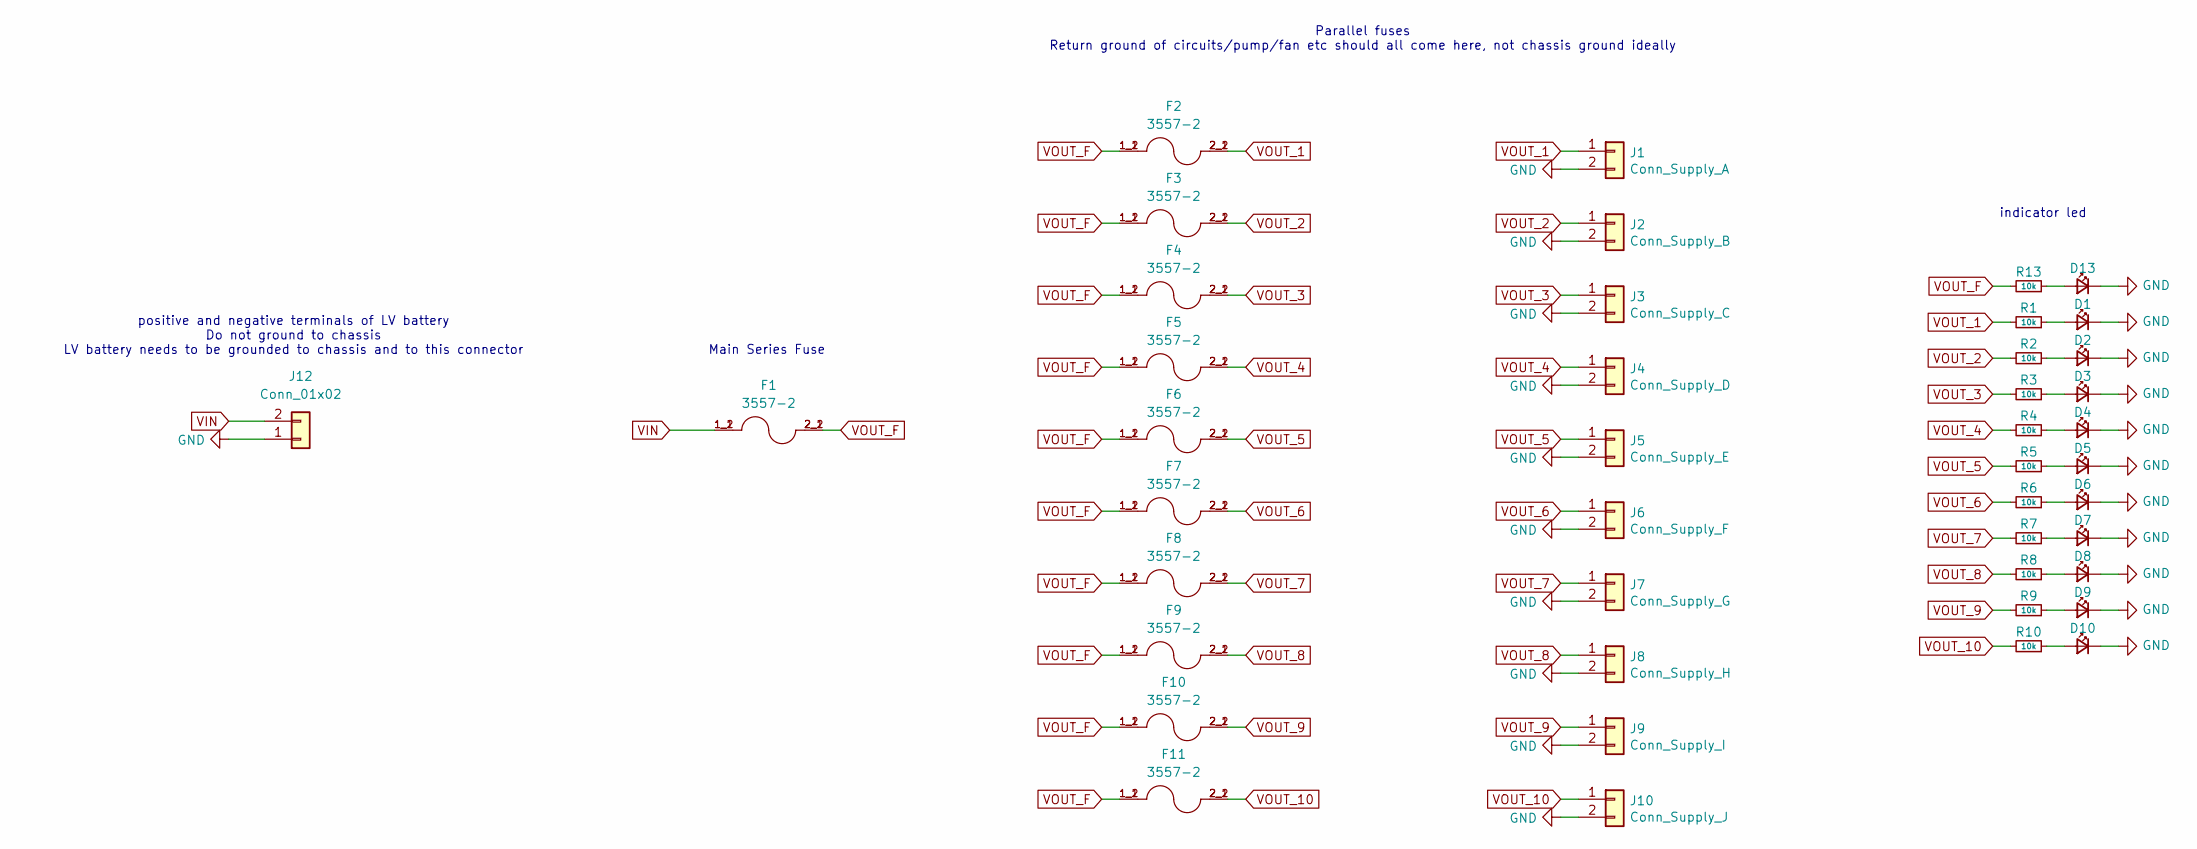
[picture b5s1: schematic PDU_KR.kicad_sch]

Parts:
D1, D2, D3, D4, D5, D6, D7, D8, D9, D10, D13: LED_Red; LED_0805_2012Metric; Manufacturer Part Number APT2012SECK/J3-PRV
F1, F2, F3, F4, F5, F6, F7, F8, F9, F10, F11: 3557-2; FUSE_3557-2; MPN 3557-2
J1: Conn_Supply_A; JST_XH_B2B-XH-A_1x02_P2.50mm_Vertical; Manufacturer Part Number B2B-XH-A
J2: Conn_Supply_B; JST_XH_B2B-XH-A_1x02_P2.50mm_Vertical; Manufacturer Part Number B2B-XH-A
J3: Conn_Supply_C; JST_XH_B2B-XH-A_1x02_P2.50mm_Vertical; Manufacturer Part Number B2B-XH-A
J4: Conn_Supply_D; JST_XH_B2B-XH-A_1x02_P2.50mm_Vertical; Manufacturer Part Number B2B-XH-A
J5: Conn_Supply_E; JST_XH_B2B-XH-A_1x02_P2.50mm_Vertical; Manufacturer Part Number B2B-XH-A
J6: Conn_Supply_F; JST_XH_B2B-XH-A_1x02_P2.50mm_Vertical; Manufacturer Part Number B2B-XH-A
J7: Conn_Supply_G; JST_XH_B2B-XH-A_1x02_P2.50mm_Vertical; Manufacturer Part Number B2B-XH-A
J8: Conn_Supply_H; JST_XH_B2B-XH-A_1x02_P2.50mm_Vertical; Manufacturer Part Number B2B-XH-A
J9: Conn_Supply_I; JST_XH_B2B-XH-A_1x02_P2.50mm_Vertical; Manufacturer Part Number B2B-XH-A
J10: Conn_Supply_J; JST_XH_B2B-XH-A_1x02_P2.50mm_Vertical; Manufacturer Part Number B2B-XH-A
J12: Conn_01x02; Phoenix_1x2_1729128; Manufacturer Part Number 1729128
R1, R2, R3, R4, R5, R6, R7, R8, R9, R10, R13: 10k; R_0805_2012Metric; Manufacturer Part Number RT0805FRE1010KL

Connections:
GND: D1.1 (K), D2.1 (K), D3.1 (K), D4.1 (K), D5.1 (K), D6.1 (K), D7.1 (K), D8.1 (K), D9.1 (K), D10.1 (K), D13.1 (K), J1.2, J2.2, J3.2, J4.2, J5.2, J6.2, J7.2, J8.2, J9.2, J10.2, J12.1
unnamed: D1.2 (A), R1.1
unnamed: D2.2 (A), R2.1
unnamed: D3.2 (A), R3.1
unnamed: D4.2 (A), R4.1
unnamed: D5.2 (A), R5.1
unnamed: D6.2 (A), R6.1
unnamed: D7.2 (A), R7.1
unnamed: D8.2 (A), R8.1
unnamed: D9.2 (A), R9.1
unnamed: D10.2 (A), R10.1
unnamed: D13.2 (A), R13.1
VIN: F1.1_1, F1.1_2, J12.2
VOUT_1: F2.2_1, F2.2_2, J1.1, R1.2
VOUT_2: F3.2_1, F3.2_2, J2.1, R2.2
VOUT_3: F4.2_1, F4.2_2, J3.1, R3.2
VOUT_4: F5.2_1, F5.2_2, J4.1, R4.2
VOUT_5: F6.2_1, F6.2_2, J5.1, R5.2
VOUT_6: F7.2_1, F7.2_2, J6.1, R6.2
VOUT_7: F8.2_1, F8.2_2, J7.1, R7.2
VOUT_8: F9.2_1, F9.2_2, J8.1, R8.2
VOUT_9: F10.2_1, F10.2_2, J9.1, R9.2
VOUT_10: F11.2_1, F11.2_2, J10.1, R10.2
VOUT_F: F1.2_1, F1.2_2, F2.1_1, F2.1_2, F3.1_1, F3.1_2, F4.1_1, F4.1_2, F5.1_1, F5.1_2, F6.1_1, F6.1_2, F7.1_1, F7.1_2, F8.1_1, F8.1_2, F9.1_1, F9.1_2, F10.1_1, F10.1_2, F11.1_1, F11.1_2, R13.2

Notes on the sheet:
positive and negative terminals of LV battery Do not ground to chassis LV battery needs to be grounded to chassis and to this connector
indicator led
Parallel fuses Return ground of circuits/pump/fan etc should all come here, not chassis ground ideally
Main Series Fuse

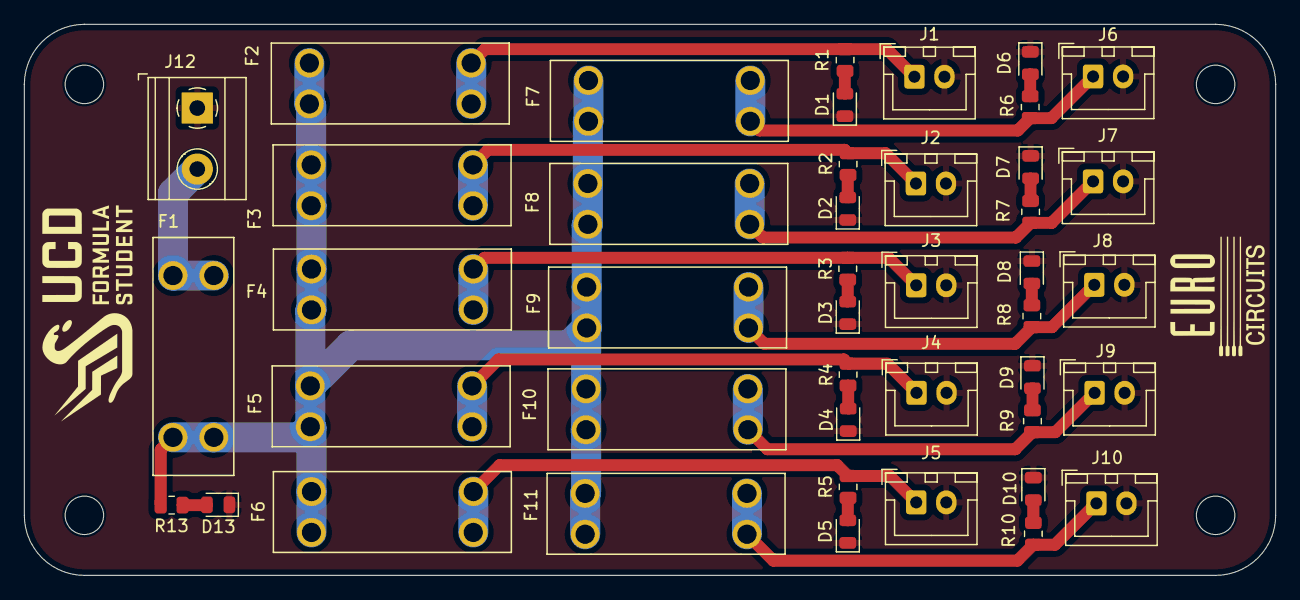
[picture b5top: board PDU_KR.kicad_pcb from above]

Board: 2 copper layers, 104.2 x 45.9 mm, 44 parts (0 on the bottom side), 24 nets.
